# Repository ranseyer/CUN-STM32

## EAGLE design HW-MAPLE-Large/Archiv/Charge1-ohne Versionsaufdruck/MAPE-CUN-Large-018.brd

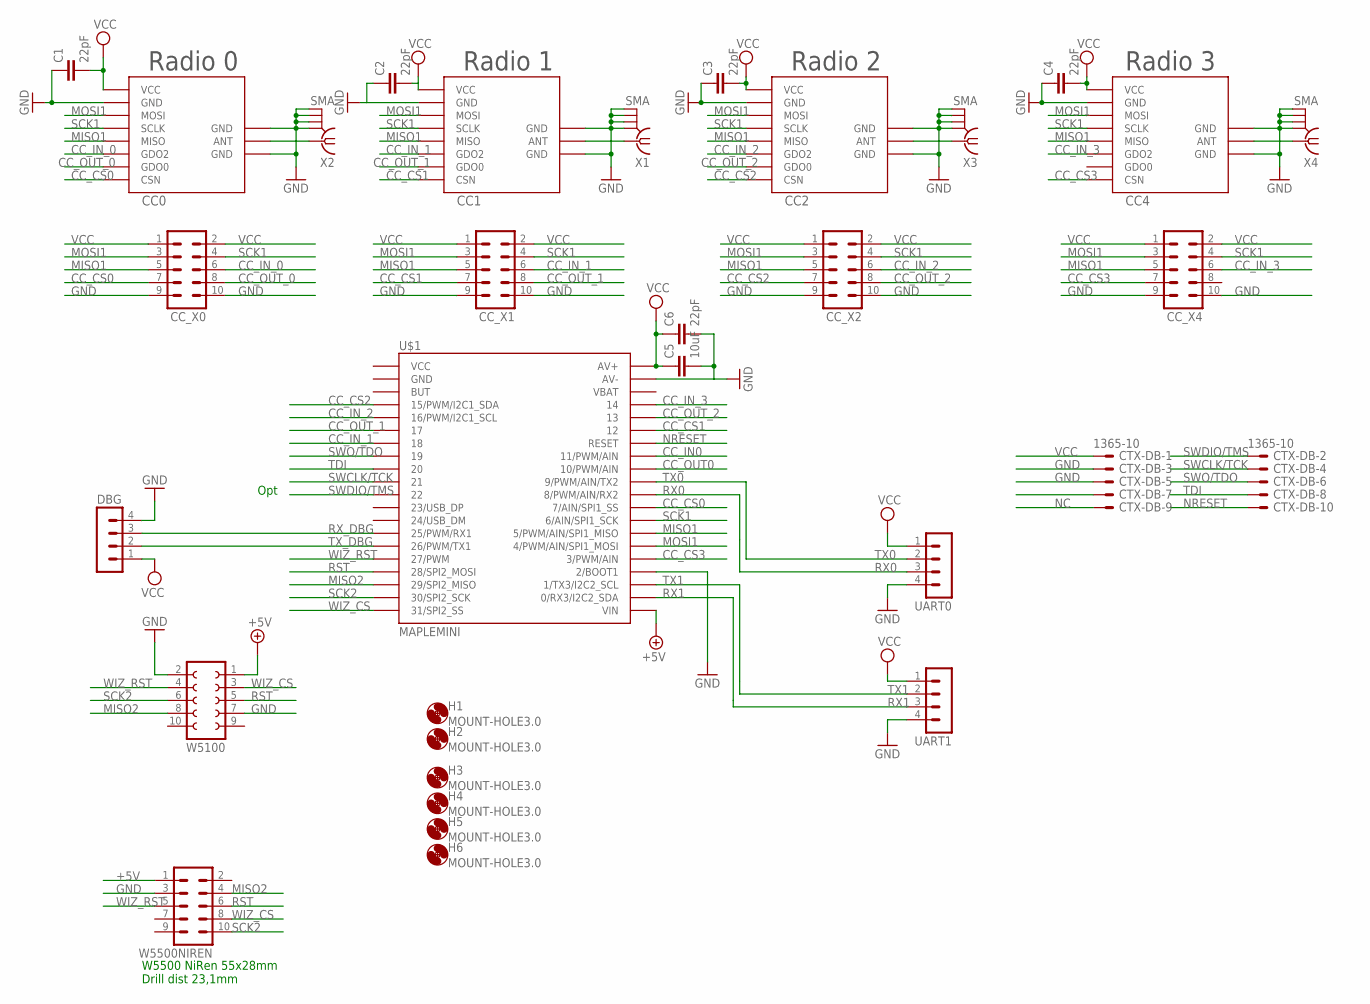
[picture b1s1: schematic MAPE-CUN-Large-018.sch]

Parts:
C1, C2, C3, C4, C6: 22pF; C0805
C5: 10uF; C1210
CC0, CC1, CC2, CC4: CC1101_MODULE1SMD; CC1101_MODULE1_SMD
CC_X0, CC_X1, CC_X2, CC_X4: MA05-2
CTX-DB: 1365-10
DBG: MA04-1
H1, H2, H3, H4, H5, H6: MOUNT-HOLE3.0; 3,0
U$1: MAPLEMINI; 20-DIP
UART0, UART1: MA04-1
W5100: FE05-2
W5500NIREN: MA05-2
X1, X2, X3, X4: SMA

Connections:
+5V: U$1.21 (VIN), W5100.1, W5500NIREN.1
CC_CS0: CC0.CSN, CC_X0.7, U$1.29 (7/AIN/SPI1_SS)
CC_CS1: CC1.CSN, CC_X1.7, U$1.35 (12)
CC_CS2: CC2.CSN, CC_X2.7, U$1.4 (15/PWM/I2C1_SDA)
CC_CS3: CC4.CSN, CC_X4.7, U$1.25 (3/PWM/AIN)
CC_IN0: U$1.33 (11/PWM/AIN)
CC_IN_0: CC0.GDO2, CC_X0.6
CC_IN_1: CC1.GDO2, CC_X1.6, U$1.7 (18)
CC_IN_2: CC2.GDO2, CC_X2.6, U$1.5 (16/PWM/I2C1_SCL)
CC_IN_3: CC4.GDO2, CC_X4.6, U$1.37 (14)
CC_OUT0: U$1.32 (10/PWM/AIN)
CC_OUT_0: CC0.GDO0, CC_X0.8
CC_OUT_1: CC1.GDO0, CC_X1.8, U$1.6 (17)
CC_OUT_2: CC2.GDO0, CC_X2.8, U$1.36 (13)
GND: C1.1, C2.1, C3.1, C4.1, C5.2, C6.2, CC0.GND@0 (GND), CC0.GND@1 (GND), CC0.GND@2 (GND), CC1.GND@0 (GND), CC1.GND@1 (GND), CC1.GND@2 (GND), CC2.GND@0 (GND), CC2.GND@1 (GND), CC2.GND@2 (GND), CC4.GND@0 (GND), CC4.GND@1 (GND), CC4.GND@2 (GND), CC_X0.9, CC_X0.10, CC_X1.9, CC_X1.10, CC_X2.9, CC_X2.10, CC_X4.9, CC_X4.10, CTX-DB.3, CTX-DB.5, DBG.4, U$1.24 (2/BOOT1), U$1.39 (AV-), UART0.4, UART1.4, W5100.2, W5100.7, W5500NIREN.3, X1.GND@1 (2), X1.GND@2 (3), X1.GND@3 (4), X1.GND@4 (5), X2.GND@1 (2), X2.GND@2 (3), X2.GND@3 (4), X2.GND@4 (5), X3.GND@1 (2), X3.GND@2 (3), X3.GND@3 (4), X3.GND@4 (5), X4.GND@1 (2), X4.GND@2 (3), X4.GND@3 (4), X4.GND@4 (5)
MISO1: CC0.MISO, CC1.MISO, CC2.MISO, CC4.MISO, CC_X0.5, CC_X1.5, CC_X2.5, CC_X4.5, U$1.27 (5/PWM/AIN/SPI1_MISO)
MISO2: U$1.18 (29/SPI2_MISO), W5100.8, W5500NIREN.4
MOSI1: CC0.MOSI, CC1.MOSI, CC2.MOSI, CC4.MOSI, CC_X0.3, CC_X1.3, CC_X2.3, CC_X4.3, U$1.26 (4/PWM/AIN/SPI1_MOSI)
unnamed: CC2.ANT, X3.1
unnamed: CC4.ANT, X4.1
unnamed: CC1.ANT, X1.1
unnamed: CC0.ANT, X2.1
NC: CTX-DB.9
NRESET: CTX-DB.10, U$1.34 (RESET)
RST: U$1.17 (28/SPI2_MOSI), W5100.5, W5500NIREN.6
RX0: U$1.30 (8/PWM/AIN/RX2), UART0.3
RX1: U$1.22 (0/RX3/I2C2_SDA), UART1.3
RX_DBG: DBG.3, U$1.14 (25/PWM/RX1)
SCK1: CC0.SCLK, CC1.SCLK, CC2.SCLK, CC4.SCLK, CC_X0.4, CC_X1.4, CC_X2.4, CC_X4.4, U$1.28 (6/AIN/SPI1_SCK)
SCK2: U$1.19 (30/SPI2_SCK), W5100.6, W5500NIREN.10
SWCLK/TCK: CTX-DB.4, U$1.10 (21)
SWDIO/TMS: CTX-DB.2, U$1.11 (22)
SWO/TDO: CTX-DB.6, U$1.8 (19)
TDI: CTX-DB.8, U$1.9 (20)
TX0: U$1.31 (9/PWM/AIN/TX2), UART0.2
TX1: U$1.23 (1/TX3/I2C2_SCL), UART1.2
TX_DBG: DBG.2, U$1.15 (26/PWM/TX1)
VCC: C1.2, C2.2, C3.2, C4.2, C5.1, C6.1, CC0.VCC, CC1.VCC, CC2.VCC, CC4.VCC, CC_X0.1, CC_X0.2, CC_X1.1, CC_X1.2, CC_X2.1, CC_X2.2, CC_X4.1, CC_X4.2, CTX-DB.1, DBG.1, U$1.40 (AV+), UART0.1, UART1.1
WIZ_CS: U$1.20 (31/SPI2_SS), W5100.3, W5500NIREN.8
WIZ_RST: U$1.16 (27/PWM), W5100.4, W5500NIREN.5

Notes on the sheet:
Radio 1
Radio 0
Opt
Radio 2
Radio 3
W5500 NiRen 55x28mm Drill dist 23,1mm

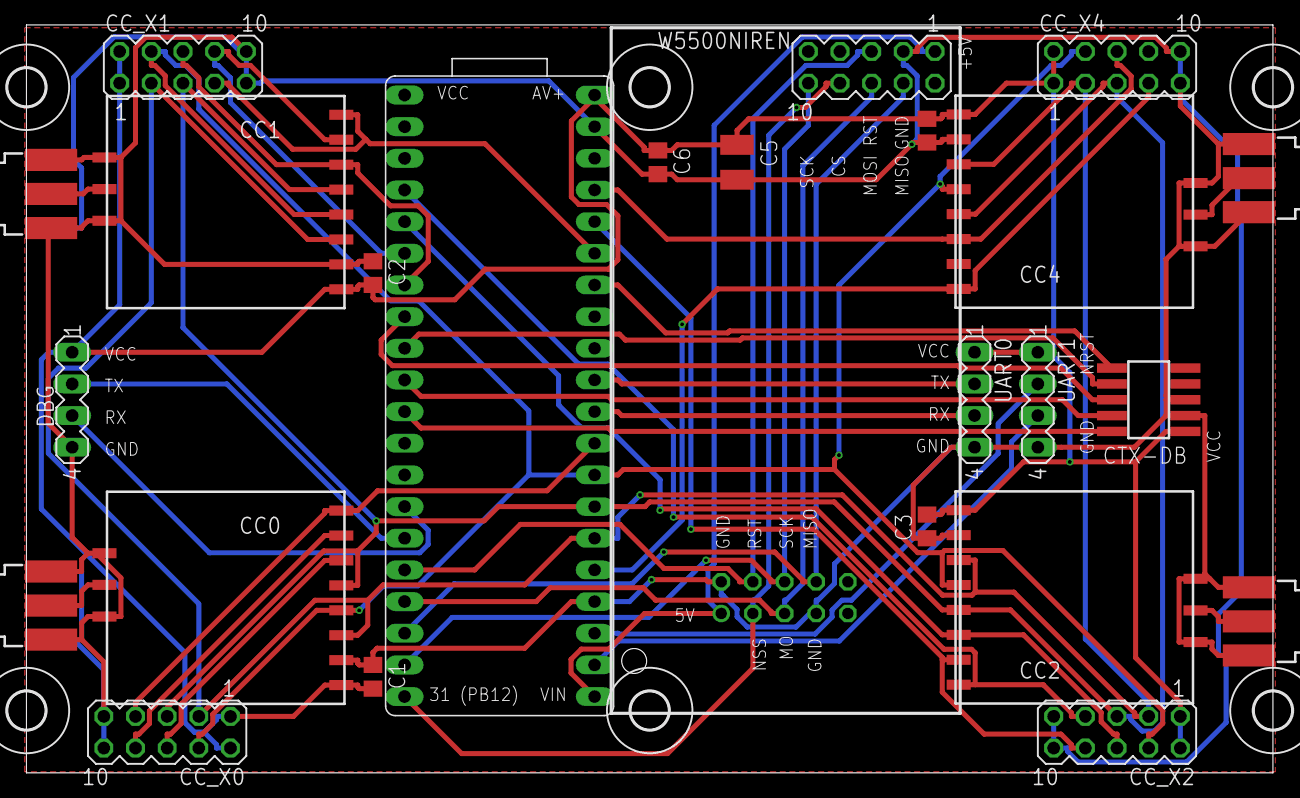
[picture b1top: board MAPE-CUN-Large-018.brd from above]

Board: 2 copper layers, 100.0 x 60.0 mm, 31 parts (1 on the bottom side), 37 nets.

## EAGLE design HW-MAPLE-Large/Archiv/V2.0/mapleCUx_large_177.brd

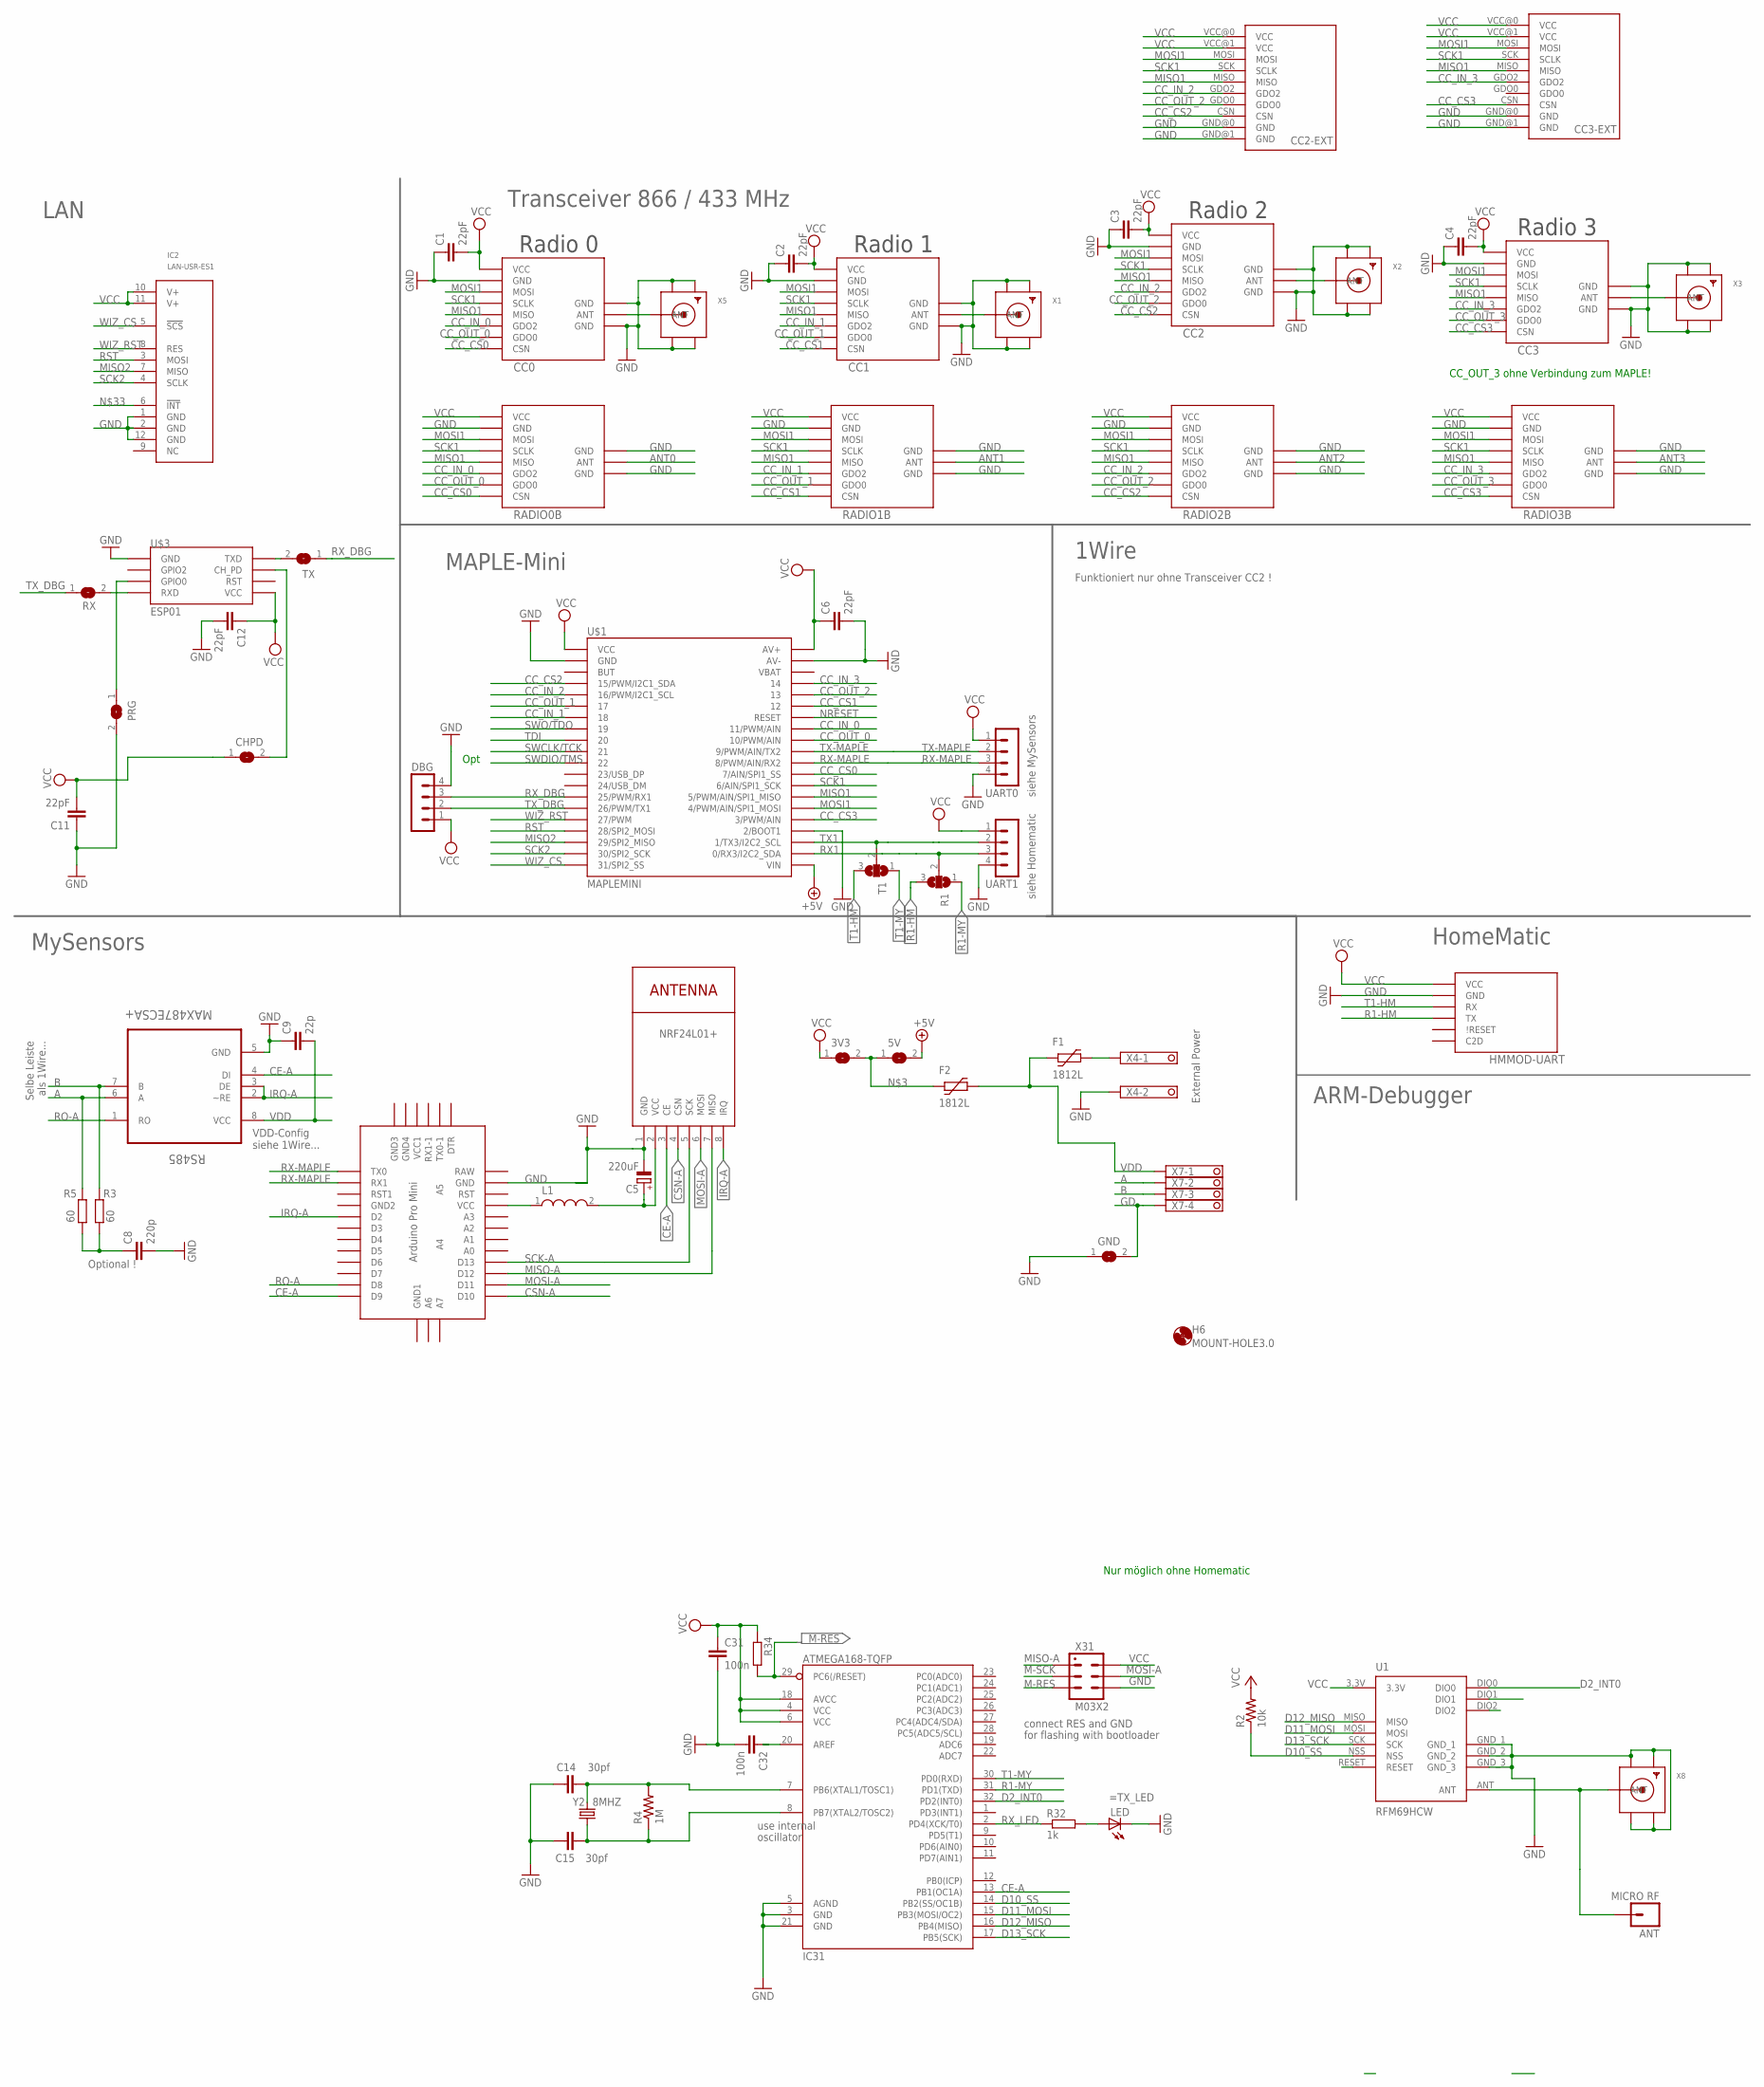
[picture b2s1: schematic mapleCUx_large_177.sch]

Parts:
3V3, 5V: SJ
ANT: MICRO RF; 1X01
C1, C2, C3, C4, C6, C11, C12: 22pF; C0805
C5: 220uF; E5-8,5
C8: 220p; C0805
C9: 22p; C0805
C14, C15: 30pf; 0805
C31, C32: 100n; C0805
CC0: CC1101; CC1101_MODULE1_SMD
CC1, CC2, CC3: CC1101_MODULE1SMD; CC1101_MODULE1_SMD
CC2-EXT, CC3-EXT: CC1101_MODULE3_DIL
CHPD: SJ
DBG: MA04-1
F1, F2: 1812L
GND: SJ
H6: MOUNT-HOLE3.0; 3,0
HMMOD-UART: HM-MOD-UARTDIL; HM-MOD-UART-DIL
IC2: LAN-USR-ES1; USR-ES1
IC31: ATMEGA168-TQFP; TQFP32-08
L1: WE-KI_0805A
LED: LEDCHIPLED_0805; CHIPLED_0805
NRF24L01+: NRF24L01+; WIRELESS-NRF24L01
PRG: SJ
R1: SJ2W; SJ_2
R2: 10k; 0805
R3, R5: 60; R0805
R4: 1M; 0805
R32: 1k; R0805
R34: R-EU_R0805; R0805
RADIO0B, RADIO1B, RADIO2B, RADIO3B: CC1101_MODULE1SMALL; CC1101_MODULE1_SMD
RS485: MAX487ECSA+; SOIC127P600X175-8N
RX: SJ
T1: SJ2W; SJ_2
TX: SJ
U1: RFM69HCW; RFM69HCW-XXXS2
U$1: MAPLEMINI; 20-DIP
U$2: ABK-PRO-MINI
U$3: ESP01
UART0, UART1: MA04-1
X1, X2, X3, X5, X8: SMACONNECTOR_EDGE_UFL; SMA_EDGELAUNCH_UFL
X4: 1751248
X7: 1751264
X31: M03X2; 2X03-1.27MM_SMD
Y2: 8MHZ; CRYSTAL-TXC-7A

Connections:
+5V: 5V.2, U$1.21 (VIN)
A: R5.2, RS485.6 (A), X7.2
ANT: ANT.1, U1.ANT, X8.P (ANT)
ANT0: CC0.ANT, RADIO0B.ANT, X5.P (ANT)
ANT1: CC1.ANT, RADIO1B.ANT, X1.P (ANT)
ANT2: CC2.ANT, RADIO2B.ANT, X2.P (ANT)
ANT3: CC3.ANT, RADIO3B.ANT, X3.P (ANT)
B: R3.2, RS485.7 (B), X7.3
CC_CS0: CC0.CSN, RADIO0B.CSN, U$1.29 (7/AIN/SPI1_SS)
CC_CS1: CC1.CSN, RADIO1B.CSN, U$1.35 (12)
CC_CS2: CC2.CSN, CC2-EXT.CSN, RADIO2B.CSN, U$1.4 (15/PWM/I2C1_SDA)
CC_CS3: CC3.CSN, CC3-EXT.CSN, RADIO3B.CSN, U$1.25 (3/PWM/AIN)
CC_IN_0: CC0.GDO2, RADIO0B.GDO2, U$1.33 (11/PWM/AIN)
CC_IN_1: CC1.GDO2, RADIO1B.GDO2, U$1.7 (18)
CC_IN_2: CC2.GDO2, CC2-EXT.GDO2, RADIO2B.GDO2, U$1.5 (16/PWM/I2C1_SCL)
CC_IN_3: CC3.GDO2, CC3-EXT.GDO2, RADIO3B.GDO2, U$1.37 (14)
CC_OUT_0: CC0.GDO0, RADIO0B.GDO0, U$1.32 (10/PWM/AIN)
CC_OUT_1: CC1.GDO0, RADIO1B.GDO0, U$1.6 (17)
CC_OUT_2: CC2.GDO0, CC2-EXT.GDO0, RADIO2B.GDO0, U$1.36 (13)
CC_OUT_3: CC3.GDO0, RADIO3B.GDO0
CE-A: IC31.13 (PB1(OC1A)), NRF24L01+.3 (CE), RS485.4 (DI), U$2.D9
CSN-A: NRF24L01+.4 (CSN), U$2.D10
D2_INT0: IC31.32 (PD2(INT0)), U1.DIO0
D10_SS: IC31.14 (PB2(SS/OC1B)), R2.1, U1.NSS
D11_MOSI: IC31.15 (PB3(MOSI/OC2)), U1.MOSI
D12_MISO: IC31.16 (PB4(MISO)), U1.MISO
D13_SCK: IC31.17 (PB5(SCK)), U1.SCK
E+: F1.P$2 (2), X4.1
GD: GND.2, X7.4
GND: C1.1, C2.1, C3.1, C4.1, C5.-, C6.2, C8.2, C9.1, C11.1, C12.2, C14.1, C15.1, C31.2, C32.2, CC0.GND@0 (GND), CC0.GND@1 (GND), CC0.GND@2 (GND), CC1.GND@0 (GND), CC1.GND@1 (GND), CC1.GND@2 (GND), CC2.GND@0 (GND), CC2.GND@1 (GND), CC2.GND@2 (GND), CC2-EXT.GND@0 (GND), CC2-EXT.GND@1 (GND), CC3.GND@0 (GND), CC3.GND@1 (GND), CC3.GND@2 (GND), CC3-EXT.GND@0 (GND), CC3-EXT.GND@1 (GND), DBG.4, GND.1, HMMOD-UART.2 (GND), IC2.1 (GND), IC2.2 (GND), IC2.12 (GND), IC31.3 (GND), IC31.5 (AGND), IC31.21 (GND), LED.C, NRF24L01+.1 (GND), PRG.2, RADIO0B.GND@0 (GND), RADIO0B.GND@1 (GND), RADIO0B.GND@2 (GND), RADIO1B.GND@0 (GND), RADIO1B.GND@1 (GND), RADIO1B.GND@2 (GND), RADIO2B.GND@0 (GND), RADIO2B.GND@1 (GND), RADIO2B.GND@2 (GND), RADIO3B.GND@0 (GND), RADIO3B.GND@1 (GND), RADIO3B.GND@2 (GND), RS485.5 (GND), U1.GND_1, U1.GND_2, U1.GND_3, U$1.2 (GND), U$1.24 (2/BOOT1), U$1.39 (AV-), U$2.GND, U$3.GND, UART0.4, UART1.4, X1.GND@1 (GND1), X1.GND@2 (GND2), X1.GND@3 (GND3), X1.GND@4 (GND4), X2.GND@1 (GND1), X2.GND@2 (GND2), X2.GND@3 (GND3), X2.GND@4 (GND4), X3.GND@1 (GND1), X3.GND@2 (GND2), X3.GND@3 (GND3), X3.GND@4 (GND4), X4.2, X5.GND@1 (GND1), X5.GND@2 (GND2), X5.GND@3 (GND3), X5.GND@4 (GND4), X8.GND@1 (GND1), X8.GND@2 (GND2), X8.GND@3 (GND3), X8.GND@4 (GND4), X31.P$6 (6)
IRQ-A: NRF24L01+.8 (IRQ), RS485.2 (~RE), RS485.3 (DE), U$2.D2
M-RES: IC31.29 (PC6(/RESET)), R34.2, X31.P$5 (5)
M-SCK: X31.P$3 (3)
MISO1: CC0.MISO, CC1.MISO, CC2.MISO, CC2-EXT.MISO, CC3.MISO, CC3-EXT.MISO, RADIO0B.MISO, RADIO1B.MISO, RADIO2B.MISO, RADIO3B.MISO, U$1.27 (5/PWM/AIN/SPI1_MISO)
MISO2: IC2.7 (MISO), U$1.18 (29/SPI2_MISO)
MISO-A: NRF24L01+.7 (MISO), U$2.D12, X31.P$1 (1)
MOSI1: CC0.MOSI, CC1.MOSI, CC2.MOSI, CC2-EXT.MOSI, CC3.MOSI, CC3-EXT.MOSI, RADIO0B.MOSI, RADIO1B.MOSI, RADIO2B.MOSI, RADIO3B.MOSI, U$1.26 (4/PWM/AIN/SPI1_MOSI)
MOSI-A: NRF24L01+.6 (MOSI), U$2.D11, X31.P$4 (4)
unnamed: C5.+, L1.2, NRF24L01+.2 (VCC)
unnamed: L1.1, U$2.VCC
unnamed: 3V3.2, 5V.1, F2.P$1 (1)
unnamed: C14.2, IC31.7 (PB6(XTAL1/TOSC1)), R4.2, Y2.P$2 (2)
unnamed: RX.2, U$3.RX (RXD)
unnamed: TX.2, U$3.TX (TXD)
unnamed: PRG.1, U$3.GPIO0
unnamed: CHPD.2, U$3.CH_PD
unnamed: C32.1, IC31.20 (AREF)
unnamed: LED.A, R32.2
unnamed: C15.2, IC31.8 (PB7(XTAL2/TOSC2)), R4.1, Y2.P$1 (1)
unnamed: C8.1, R3.1, R5.1
NRESET: U$1.34 (RESET)
R1-HM: HMMOD-UART.5 (TX), R1.3
R1-MY: IC31.31 (PD1(TXD)), R1.1
RO-A: RS485.1 (RO), U$2.D8
RST: IC2.3 (MOSI), U$1.17 (28/SPI2_MOSI)
RX1: R1.2, U$1.22 (0/RX3/I2C2_SDA), UART1.3
RX-MAPLE: U$1.30 (8/PWM/AIN/RX2), U$2.RX1, U$2.TX0, UART0.3
RX_DBG: DBG.3, TX.1, U$1.14 (25/PWM/RX1)
RX_LED: IC31.2 (PD4(XCK/T0)), R32.1
SCK1: CC0.SCLK, CC1.SCLK, CC2.SCLK, CC2-EXT.SCK (SCLK), CC3.SCLK, CC3-EXT.SCK (SCLK), RADIO0B.SCLK, RADIO1B.SCLK, RADIO2B.SCLK, RADIO3B.SCLK, U$1.28 (6/AIN/SPI1_SCK)
SCK2: IC2.4 (SCLK), U$1.19 (30/SPI2_SCK)
SCK-A: NRF24L01+.5 (SCK), U$2.D13
SWCLK/TCK: U$1.10 (21)
SWDIO/TMS: U$1.11 (22)
SWO/TDO: U$1.8 (19)
T1-HM: HMMOD-UART.6 (RX), T1.3
T1-MY: IC31.30 (PD0(RXD)), T1.1
TDI: U$1.9 (20)
TX1: T1.2, U$1.23 (1/TX3/I2C2_SCL), UART1.2
TX-MAPLE: U$1.31 (9/PWM/AIN/TX2), UART0.2
TX_DBG: DBG.2, RX.1, U$1.15 (26/PWM/TX1)
VCC: 3V3.1, C1.2, C2.2, C3.2, C4.2, C6.1, C11.2, C12.1, C31.1, CC0.VCC, CC1.VCC, CC2.VCC, CC2-EXT.VCC@0 (VCC), CC2-EXT.VCC@1 (VCC), CC3.VCC, CC3-EXT.VCC@0 (VCC), CC3-EXT.VCC@1 (VCC), CHPD.1, DBG.1, HMMOD-UART.1 (VCC), IC2.10 (V+), IC2.11 (V+), IC31.4 (VCC), IC31.6 (VCC), IC31.18 (AVCC), R2.2, R34.1, RADIO0B.VCC, RADIO1B.VCC, RADIO2B.VCC, RADIO3B.VCC, U1.3.3V, U$1.1 (VCC), U$1.40 (AV+), U$3.VCC, UART0.1, UART1.1, X31.P$2 (2)
VDD: C9.2, F1.P$1 (1), F2.P$2 (2), RS485.8 (VCC), X7.1
WIZ_CS: IC2.5 (!SCS!), U$1.20 (31/SPI2_SS)
WIZ_RST: IC2.8 (RES), U$1.16 (27/PWM)

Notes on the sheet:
Radio 1
Radio 0
Opt
Radio 2
Radio 3
siehe Homematic
siehe MySensors
1Wire
MySensors
HomeMatic
MAPLE-Mini
Transceiver 866 / 433 MHz
LAN
External Power
Funktioniert nur ohne Transceiver CC2 !
Selbe Leiste als 1Wire...
VDD-Config siehe 1Wire...
ARM-Debugger
Optional !
CC_OUT_3 ohne Verbindung zum MAPLE!
use internal
oscillator
=TX_LED
connect RES and GND
for flashing with bootloader
Nur möglich ohne Homematic

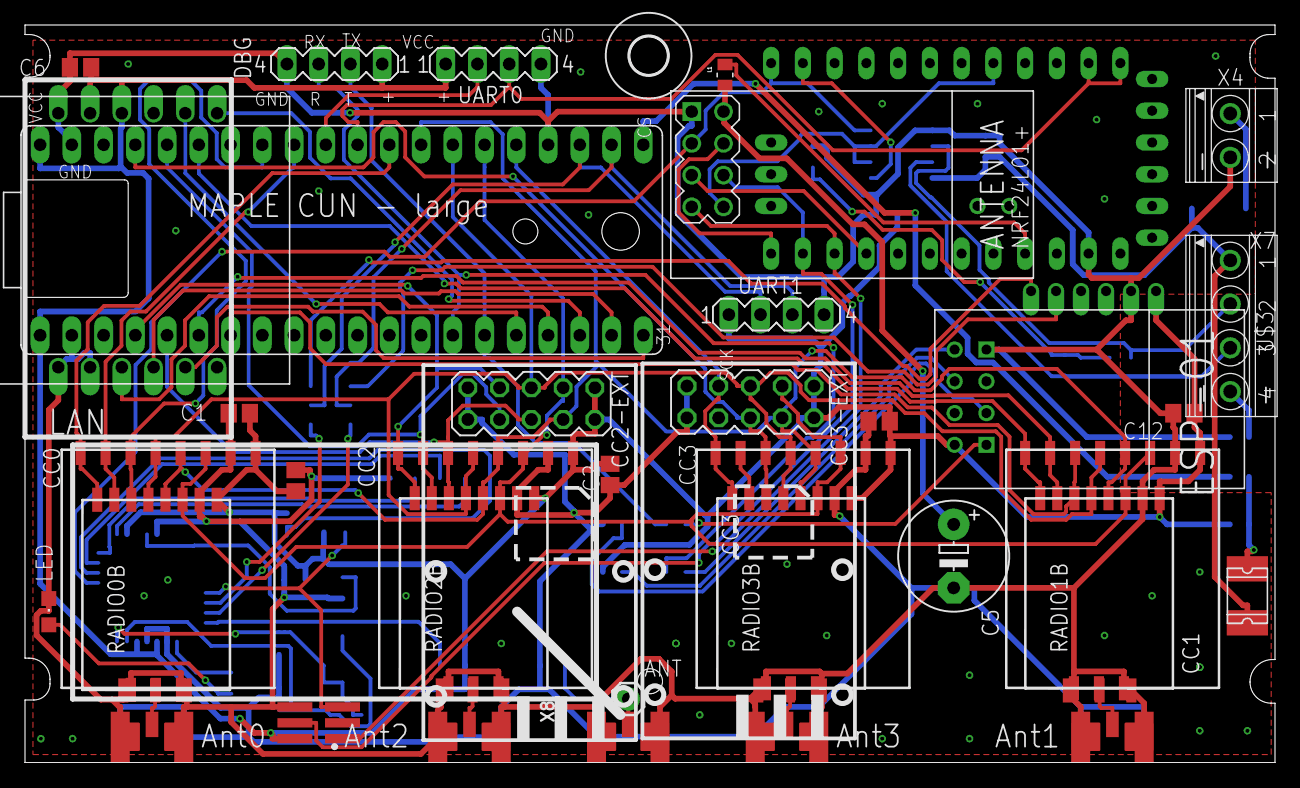
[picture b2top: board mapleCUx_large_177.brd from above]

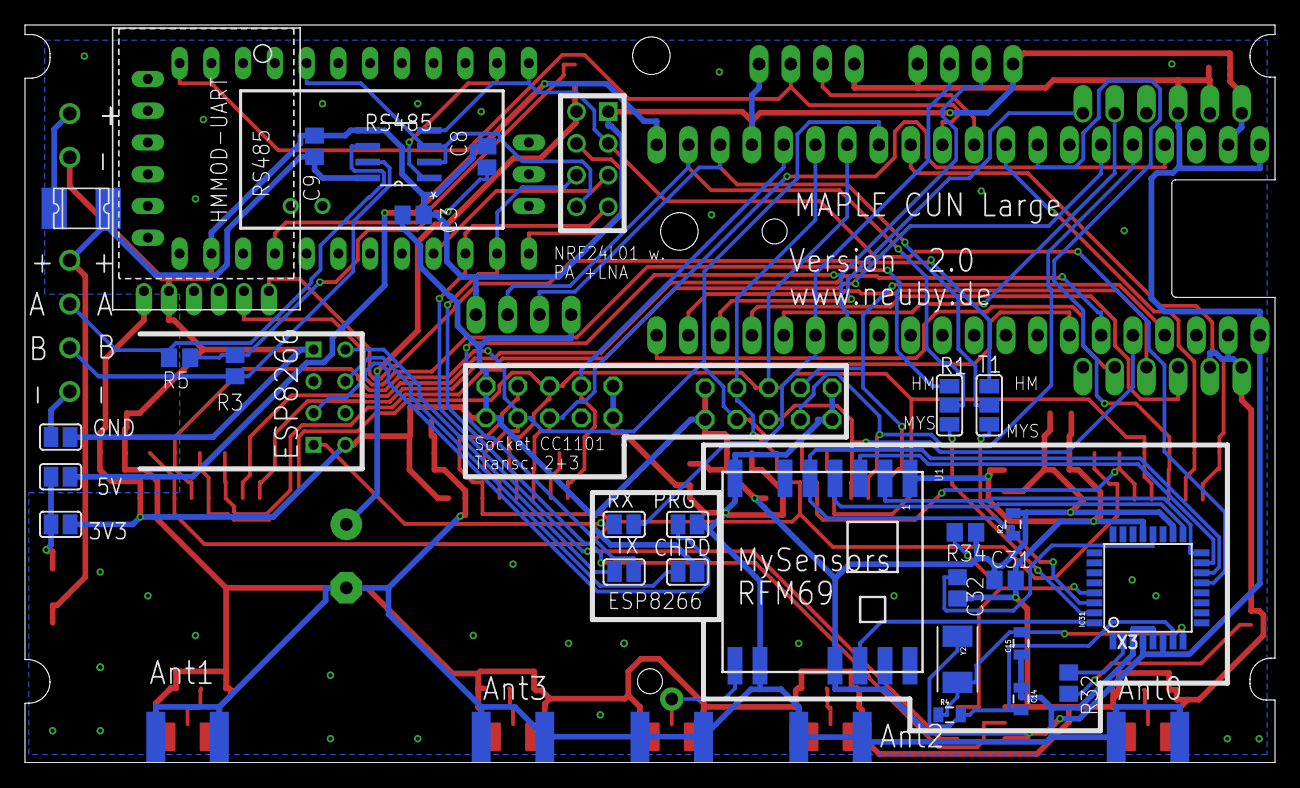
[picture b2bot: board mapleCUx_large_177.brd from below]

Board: 2 copper layers, 100.0 x 59.0 mm, 66 parts (28 on the bottom side), 69 nets.

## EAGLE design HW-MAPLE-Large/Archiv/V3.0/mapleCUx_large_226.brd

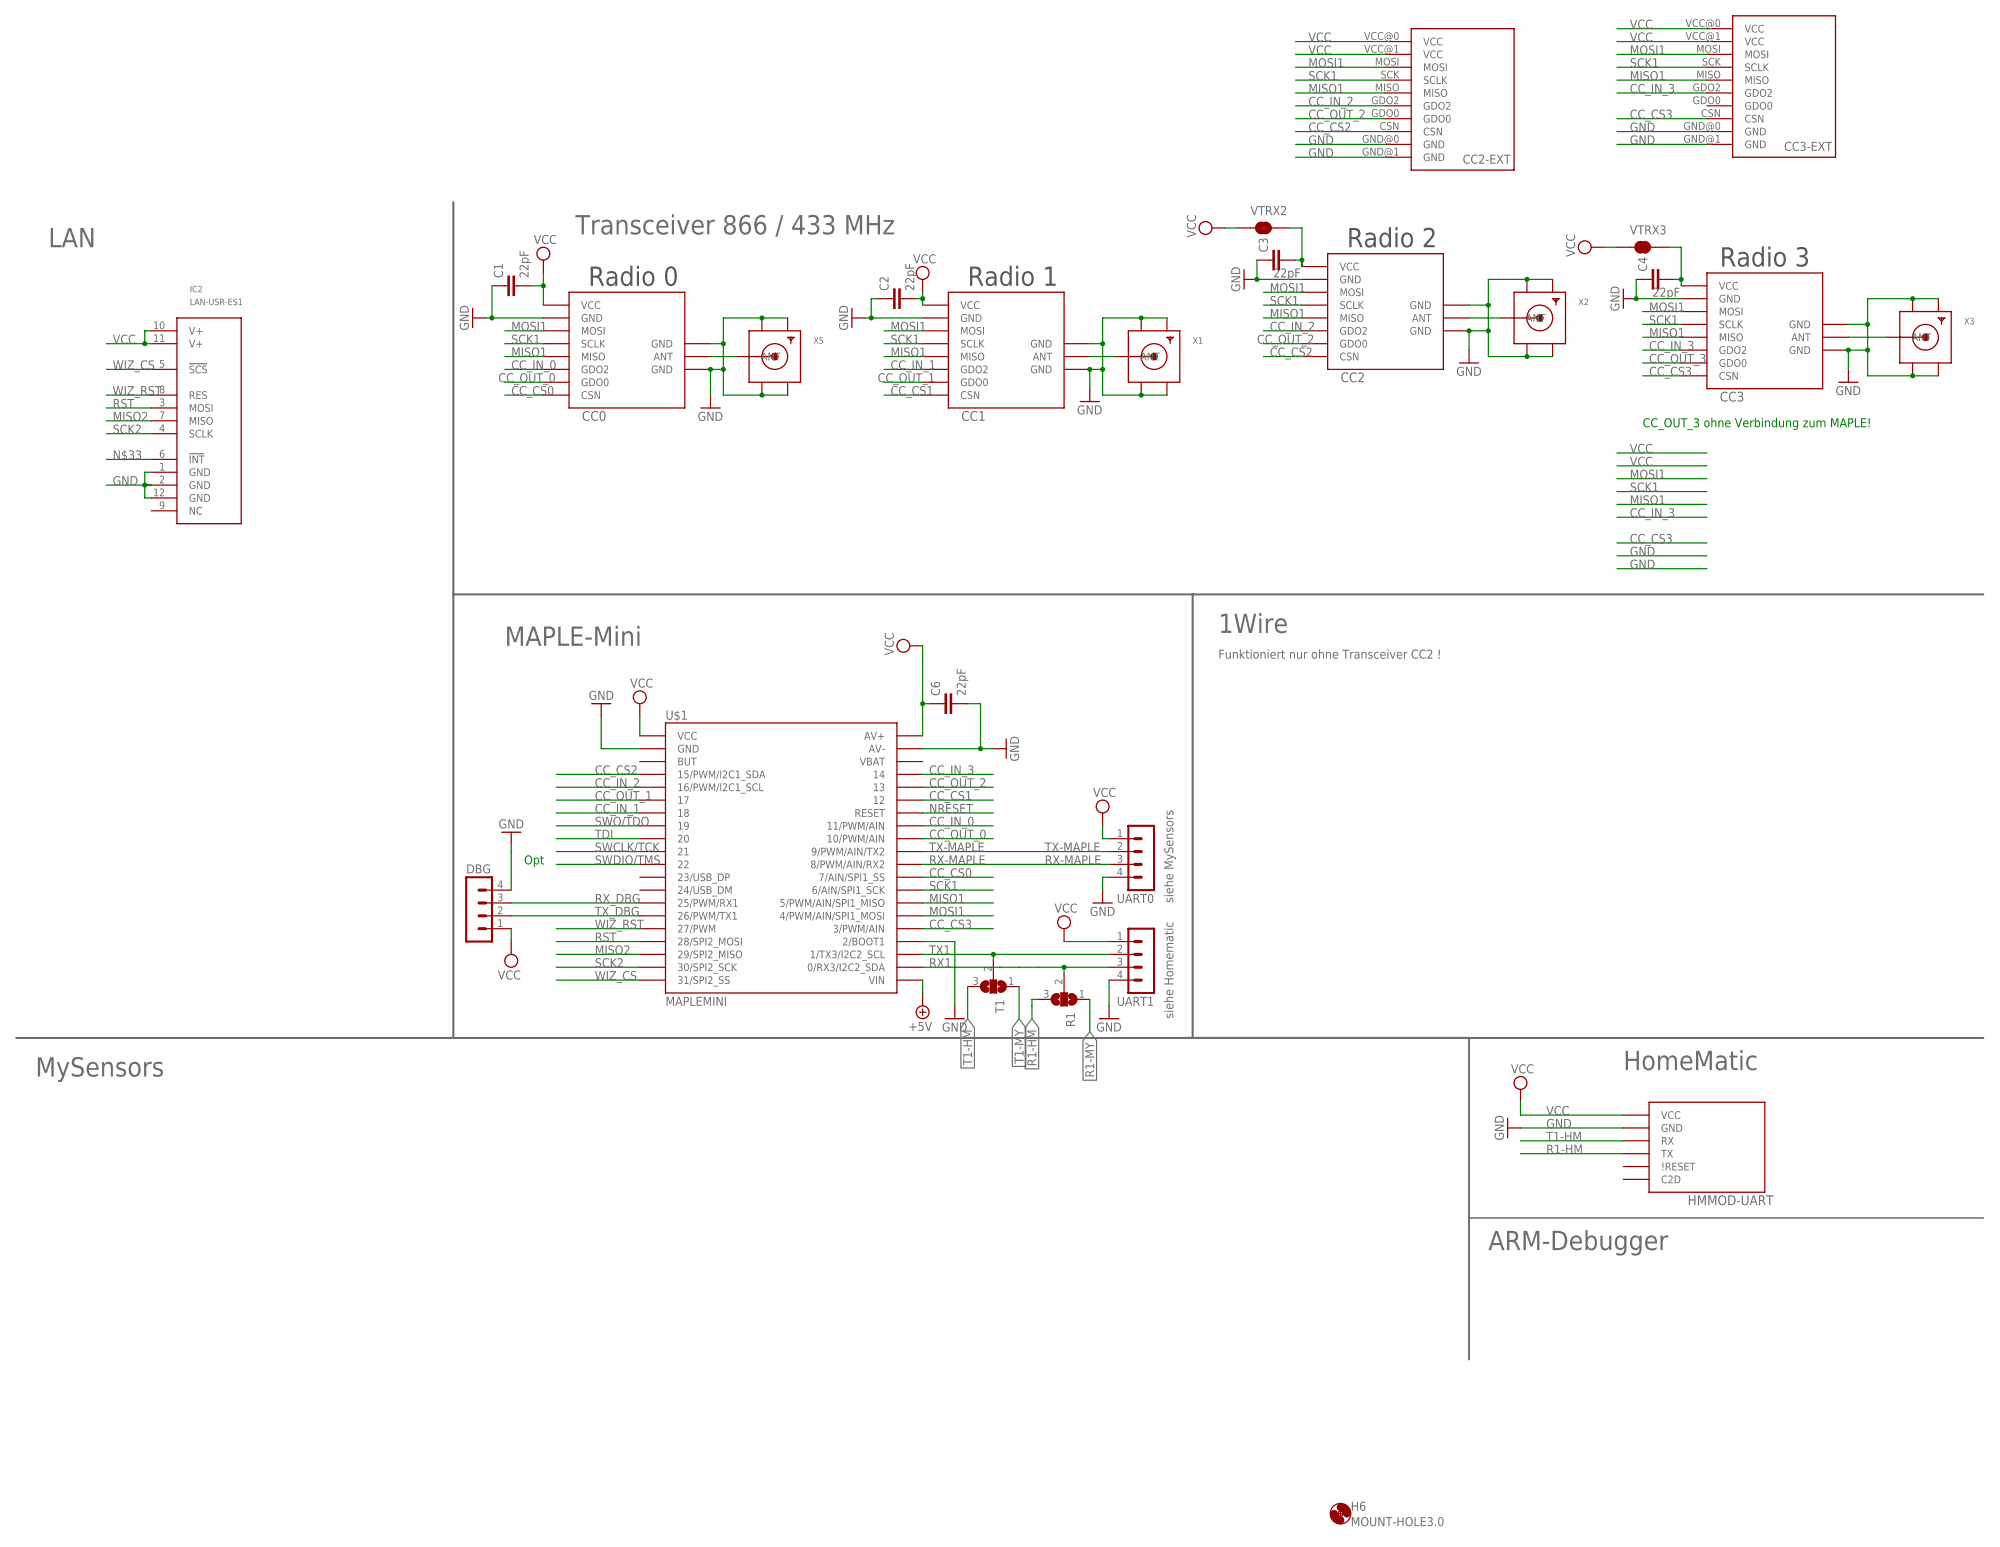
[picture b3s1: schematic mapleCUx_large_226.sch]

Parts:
C1, C2, C3, C4, C6: 22pF; C0805
CC0: CC1101; CC1101_MODULE1_SMD
CC1, CC2, CC3: CC1101_MODULE1SMD; CC1101_MODULE1_SMD
CC2-EXT, CC3-EXT: CC1101_MODULE3_DIL
DBG: MA04-1
H6: MOUNT-HOLE3.0; 3,0
HMMOD-UART: HM-MOD-UARTDIL; HM-MOD-UART-DIL
IC2: LAN-USR-ES1; USR-ES1
R1: SJ2W; SJ_2
T1: SJ2W; SJ_2
U$1: MAPLEMINI; 20-DIP
UART0, UART1: MA04-1
VTRX2, VTRX3: JUMPER-SMT_2_NC_TRACE_SILK; SMT-JUMPER_2_NC_TRACE_SILK
X1, X2, X3, X5: SMACONNECTOR_EDGE; SMA_EDGELAUNCH

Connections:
+5V: U$1.21 (VIN)
ANT0: CC0.ANT, X5.P (ANT)
ANT1: CC1.ANT, X1.P (ANT)
ANT2: CC2.ANT, X2.P (ANT)
ANT3: CC3.ANT, X3.P (ANT)
CC_CS0: CC0.CSN, U$1.29 (7/AIN/SPI1_SS)
CC_CS1: CC1.CSN, U$1.35 (12)
CC_CS2: CC2.CSN, CC2-EXT.CSN, U$1.4 (15/PWM/I2C1_SDA)
CC_CS3: CC3.CSN, CC3-EXT.CSN, U$1.25 (3/PWM/AIN)
CC_IN_0: CC0.GDO2, U$1.33 (11/PWM/AIN)
CC_IN_1: CC1.GDO2, U$1.7 (18)
CC_IN_2: CC2.GDO2, CC2-EXT.GDO2, U$1.5 (16/PWM/I2C1_SCL)
CC_IN_3: CC3.GDO2, CC3-EXT.GDO2, U$1.37 (14)
CC_OUT_0: CC0.GDO0, U$1.32 (10/PWM/AIN)
CC_OUT_1: CC1.GDO0, U$1.6 (17)
CC_OUT_2: CC2.GDO0, CC2-EXT.GDO0, U$1.36 (13)
CC_OUT_3: CC3.GDO0
GND: C1.1, C2.1, C3.1, C4.1, C6.2, CC0.GND@0 (GND), CC0.GND@1 (GND), CC0.GND@2 (GND), CC1.GND@0 (GND), CC1.GND@1 (GND), CC1.GND@2 (GND), CC2.GND@0 (GND), CC2.GND@1 (GND), CC2.GND@2 (GND), CC2-EXT.GND@0 (GND), CC2-EXT.GND@1 (GND), CC3.GND@0 (GND), CC3.GND@1 (GND), CC3.GND@2 (GND), CC3-EXT.GND@0 (GND), CC3-EXT.GND@1 (GND), DBG.4, HMMOD-UART.2 (GND), IC2.1 (GND), IC2.2 (GND), IC2.12 (GND), U$1.2 (GND), U$1.24 (2/BOOT1), U$1.39 (AV-), UART0.4, UART1.4, X1.GND@1 (GND4), X1.GND@2 (GND3), X1.GND@3 (GND2), X1.GND@4 (GND1), X2.GND@1 (GND4), X2.GND@2 (GND3), X2.GND@3 (GND2), X2.GND@4 (GND1), X3.GND@1 (GND4), X3.GND@2 (GND3), X3.GND@3 (GND2), X3.GND@4 (GND1), X5.GND@1 (GND4), X5.GND@2 (GND3), X5.GND@3 (GND2), X5.GND@4 (GND1)
MISO1: CC0.MISO, CC1.MISO, CC2.MISO, CC2-EXT.MISO, CC3.MISO, CC3-EXT.MISO, U$1.27 (5/PWM/AIN/SPI1_MISO)
MISO2: IC2.7 (MISO), U$1.18 (29/SPI2_MISO)
MOSI1: CC0.MOSI, CC1.MOSI, CC2.MOSI, CC2-EXT.MOSI, CC3.MOSI, CC3-EXT.MOSI, U$1.26 (4/PWM/AIN/SPI1_MOSI)
unnamed: C3.2, CC2.VCC, VTRX2.2
unnamed: C4.2, CC3.VCC, VTRX3.2
NRESET: U$1.34 (RESET)
R1-HM: HMMOD-UART.5 (TX), R1.3
R1-MY: R1.1
RST: IC2.3 (MOSI), U$1.17 (28/SPI2_MOSI)
RX1: R1.2, U$1.22 (0/RX3/I2C2_SDA), UART1.3
RX-MAPLE: U$1.30 (8/PWM/AIN/RX2), UART0.3
RX_DBG: DBG.3, U$1.14 (25/PWM/RX1)
SCK1: CC0.SCLK, CC1.SCLK, CC2.SCLK, CC2-EXT.SCK (SCLK), CC3.SCLK, CC3-EXT.SCK (SCLK), U$1.28 (6/AIN/SPI1_SCK)
SCK2: IC2.4 (SCLK), U$1.19 (30/SPI2_SCK)
SWCLK/TCK: U$1.10 (21)
SWDIO/TMS: U$1.11 (22)
SWO/TDO: U$1.8 (19)
T1-HM: HMMOD-UART.6 (RX), T1.3
T1-MY: T1.1
TDI: U$1.9 (20)
TX1: T1.2, U$1.23 (1/TX3/I2C2_SCL), UART1.2
TX-MAPLE: U$1.31 (9/PWM/AIN/TX2), UART0.2
TX_DBG: DBG.2, U$1.15 (26/PWM/TX1)
VCC: C1.2, C2.2, C6.1, CC0.VCC, CC1.VCC, CC2-EXT.VCC@0 (VCC), CC2-EXT.VCC@1 (VCC), CC3-EXT.VCC@0 (VCC), CC3-EXT.VCC@1 (VCC), DBG.1, HMMOD-UART.1 (VCC), IC2.10 (V+), IC2.11 (V+), U$1.1 (VCC), U$1.40 (AV+), UART0.1, UART1.1, VTRX2.1, VTRX3.1
WIZ_CS: IC2.5 (!SCS!), U$1.20 (31/SPI2_SS)
WIZ_RST: IC2.8 (RES), U$1.16 (27/PWM)

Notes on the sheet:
Radio 1
Radio 0
Opt
Radio 2
Radio 3
siehe Homematic
siehe MySensors
1Wire
MySensors
HomeMatic
MAPLE-Mini
Transceiver 866 / 433 MHz
LAN
Funktioniert nur ohne Transceiver CC2 !
ARM-Debugger
CC_OUT_3 ohne Verbindung zum MAPLE!

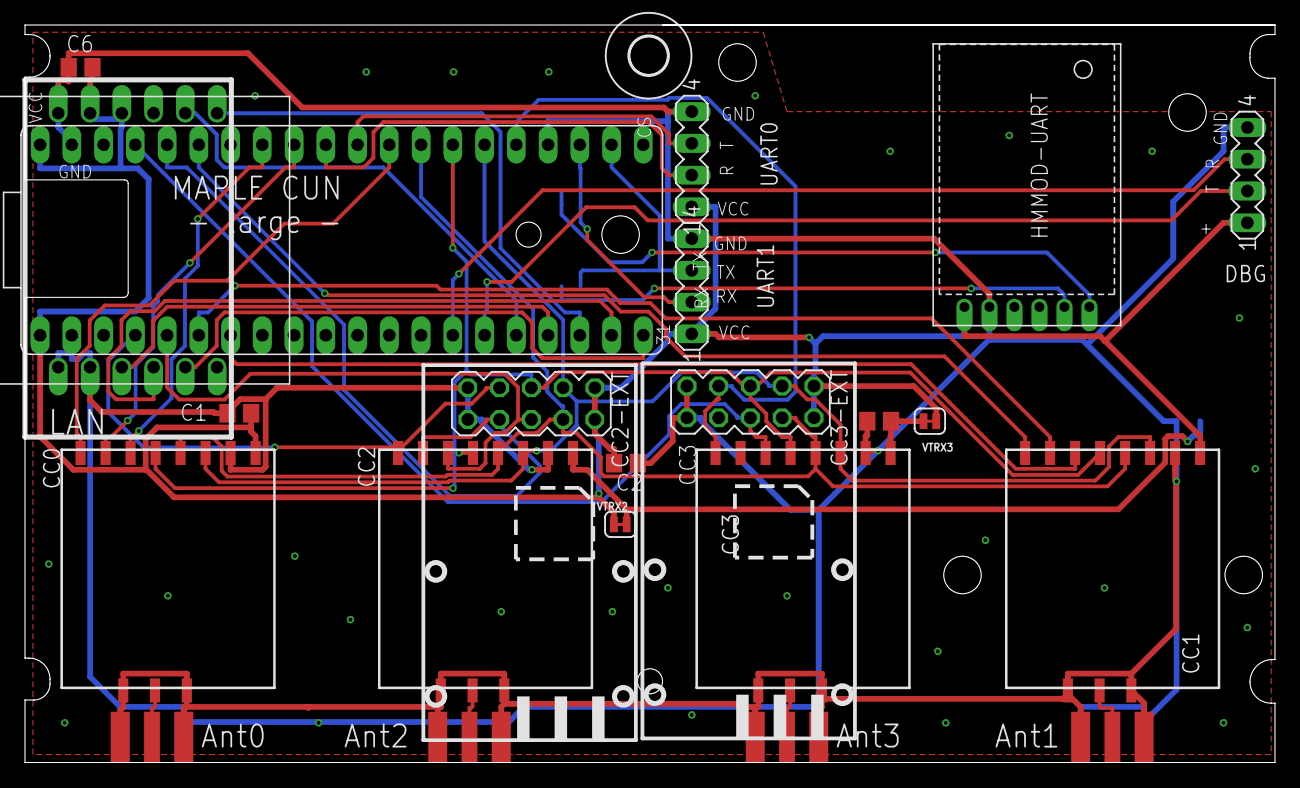
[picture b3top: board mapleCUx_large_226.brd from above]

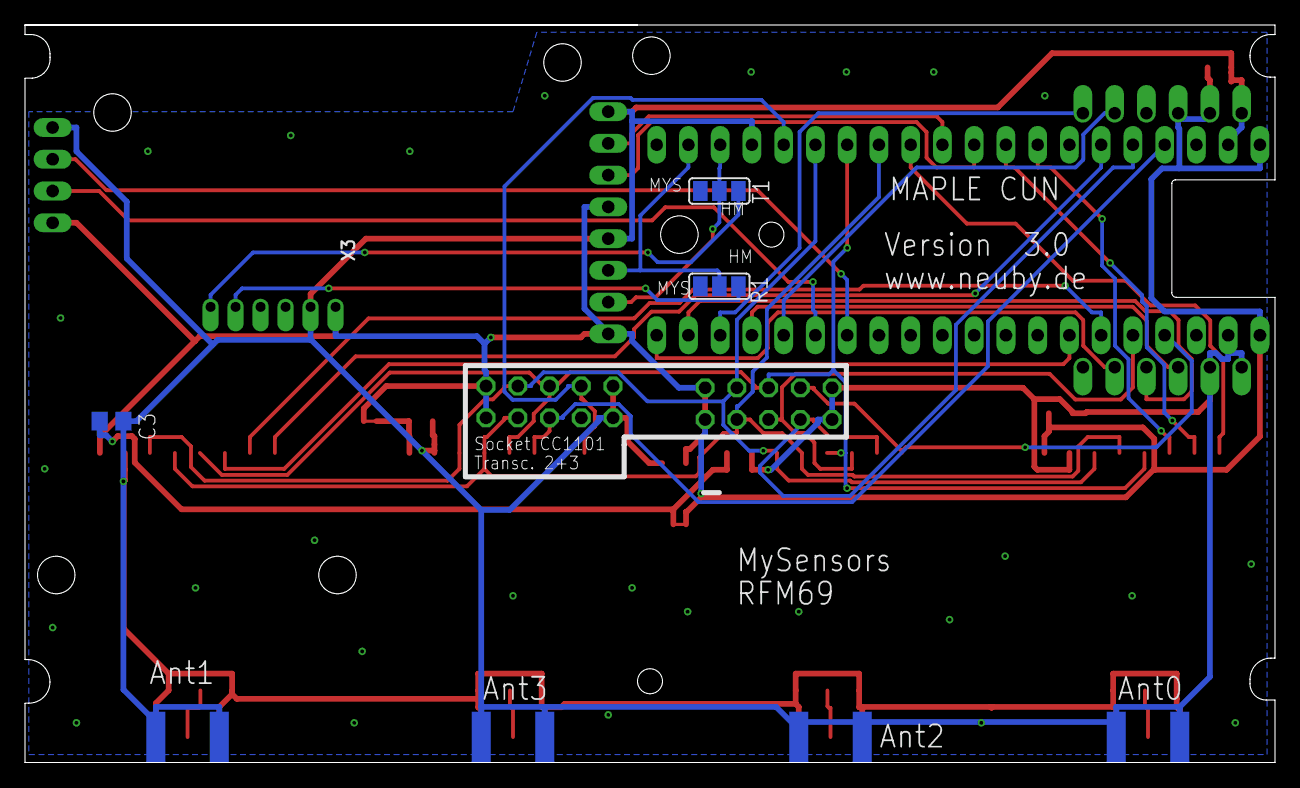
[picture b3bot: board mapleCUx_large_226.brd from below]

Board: 2 copper layers, 100.0 x 59.0 mm, 26 parts (3 on the bottom side), 35 nets.

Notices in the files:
parts and their libraries:
diy-modules: Released under the Creative Commons Attribution 4.0 International License: http://creativecommons.org/licenses/by/4.0
EAGLE-EMC_COMPONENTS-rev17a: Copyright: Würth Elektronik
